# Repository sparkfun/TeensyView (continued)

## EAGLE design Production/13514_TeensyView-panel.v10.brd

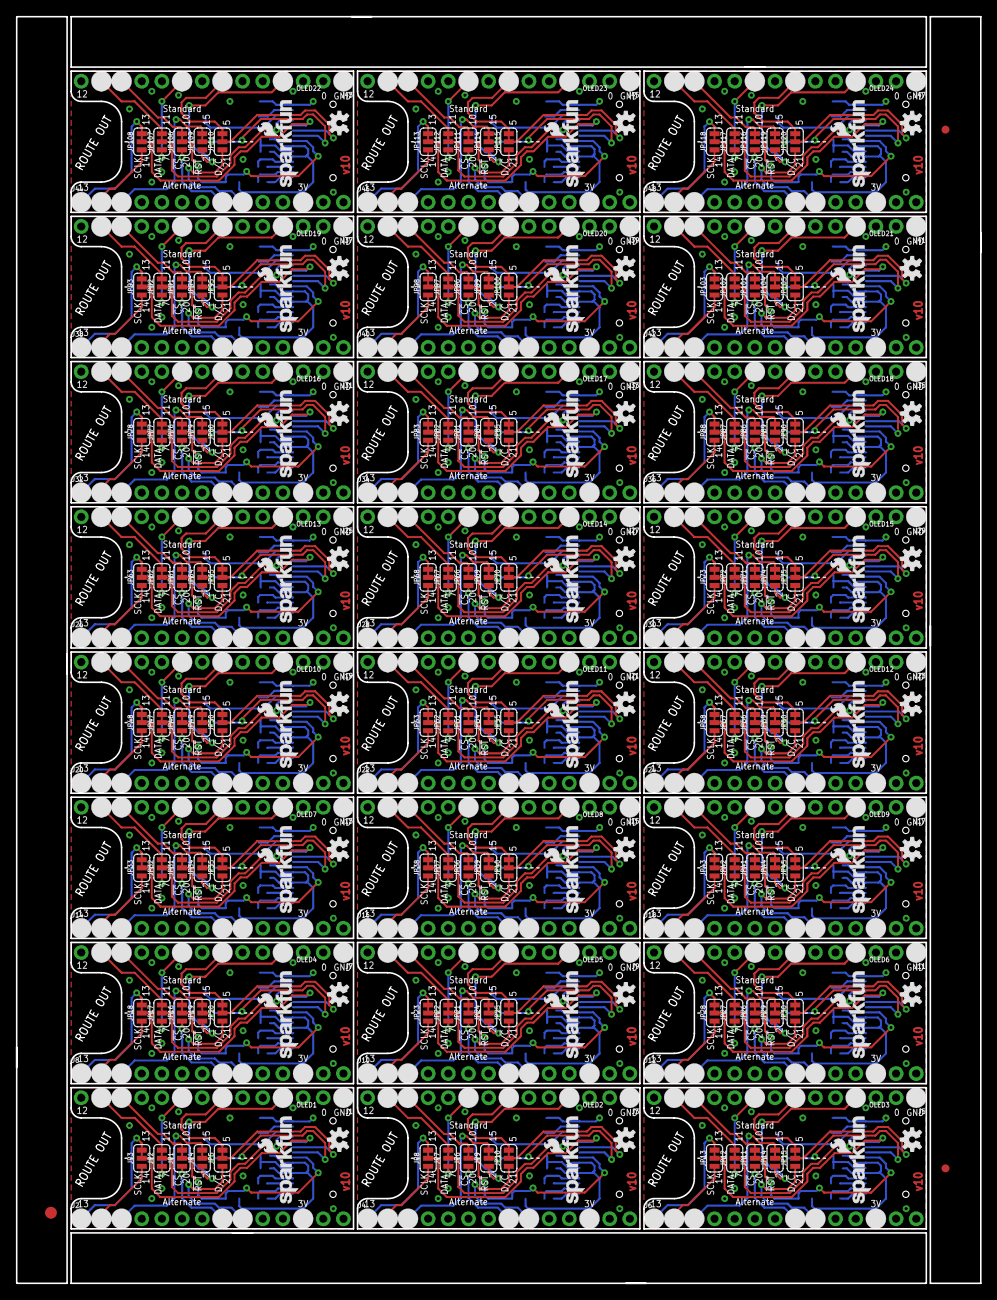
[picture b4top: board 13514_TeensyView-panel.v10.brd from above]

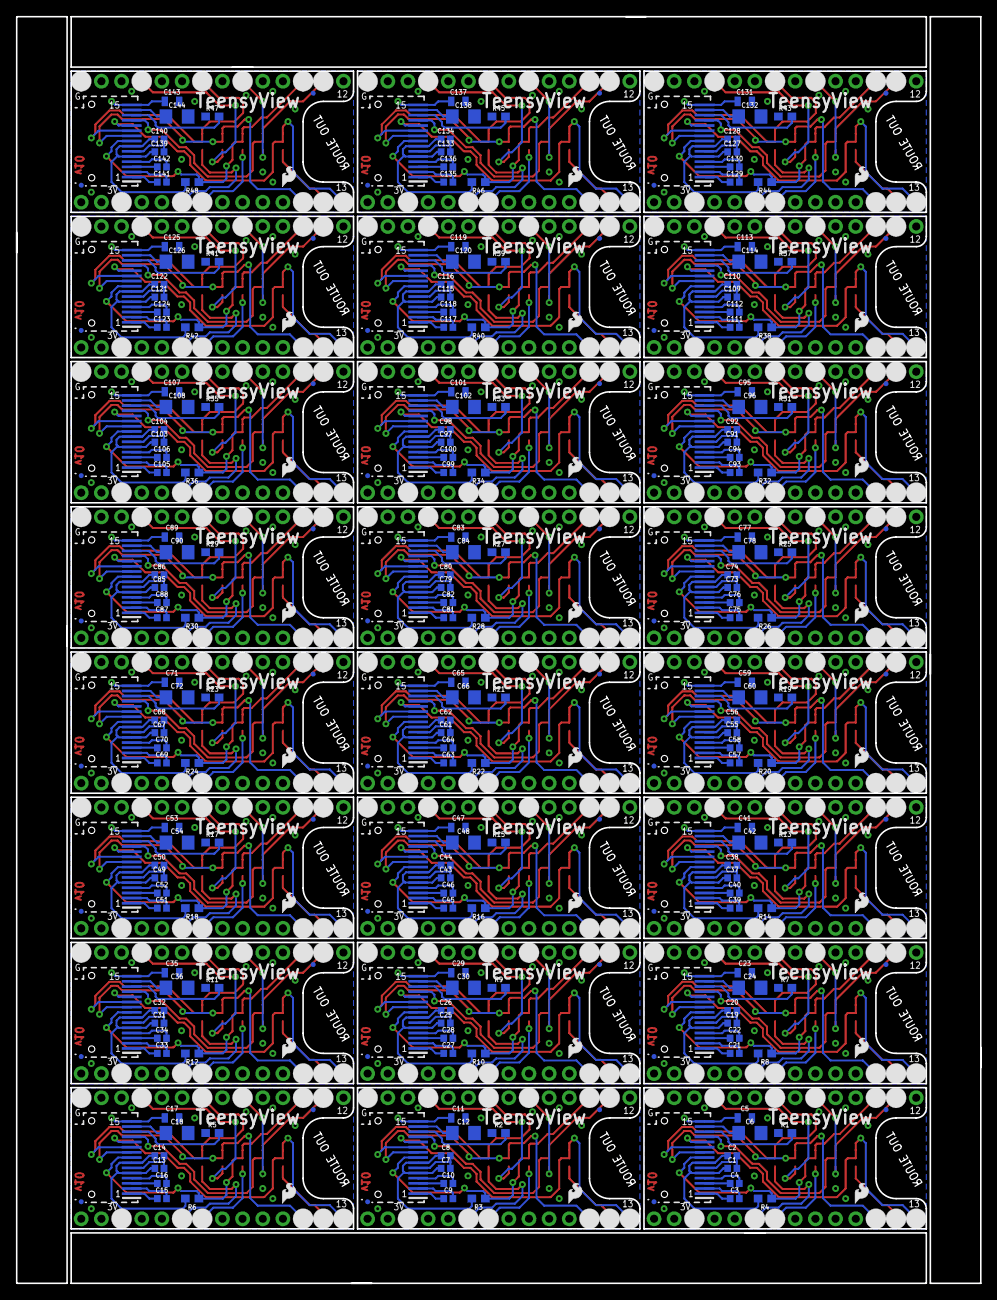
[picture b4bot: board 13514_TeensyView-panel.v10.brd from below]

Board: 2 copper layers, 121.4 x 159.5 mm, 531 parts (288 on the bottom side), 576 nets.

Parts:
C1, C2, C3, C4, C7, C8, C9, C10, C13, C14, C15, C16, C19, C20, C21, C22, C25, C26, C27, C28, C31, C32, C33, C34, C37, C38, C39, C40, C43, C44, C45, C46, C49, C50, C51, C52, C55, C56, C57, C58, C61, C62, C63, C64, C67, C68, C69, C70, C73, C74, C75, C76, C79, C80, C81, C82, C85, C86, C87, C88, C91, C92, C93, C94, C97, C98, C99, C100, C103, C104, C105, C106, C109, C110, C111, C112, C115, C116, C117, C118, C121, C122, C123, C124, C127, C128, C129, C130, C133, C134, C135, C136, C139, C140, C141, C142: 1.0uF; 0402
C5, C11, C17, C23, C29, C35, C41, C47, C53, C59, C65, C71, C77, C83, C89, C95, C101, C107, C113, C119, C125, C131, C137, C143: 2.2uF; 0805
C6, C12, C18, C24, C30, C36, C42, C48, C54, C60, C66, C72, C78, C84, C90, C96, C102, C108, C114, C120, C126, C132, C138, C144: 4.7uF; 1206
E$1: FIDUCIAL-1.5X3
E$7, E$8: FIDUCIAL-1X2
FD1, FD2, FD3, FD4, FD5, FD6, FD7, FD8, FD9, FD10, FD11, FD12, FD13, FD14, FD15, FD16, FD17, FD18, FD19, FD20, FD21, FD22, FD23, FD24, FD25, FD26, FD27, FD28, FD29, FD30, FD31, FD32, FD33, FD34, FD35, FD36, FD37, FD38, FD39, FD40, FD41, FD42, FD43, FD44, FD45, FD46, FD47, FD48: FIDUCIALUFIDUCIAL; FIDUCIAL-MICRO
J1, J2, J3, J4, J5, J6, J7, J8, J9, J10, J11, J12, J13, J14, J15, J16, J17, J18, J19, J20, J21, J22, J23, J24, J25, J26, J27, J28, J29, J30, J31, J32, J33, J34, J35, J36, J37, J38, J39, J40, J41, J42, J43, J44, J45, J46, J47, J48: DNP; 1X14_NO_SILK
JP1, JP2, JP3, JP4, JP5, JP6, JP7, JP8, JP9, JP10, JP11, JP12, JP13, JP14, JP15, JP16, JP17, JP18, JP19, JP20, JP21, JP22, JP23, JP24, JP25, JP26, JP27, JP28, JP29, JP30, JP31, JP32, JP33, JP34, JP35, JP36, JP37, JP38, JP39, JP40, JP41, JP42, JP43, JP44, JP45, JP46, JP47, JP48, JP49, JP50, JP51, JP52, JP53, JP54, JP55, JP56, JP57, JP58, JP59, JP60, JP61, JP62, JP63, JP64, JP65, JP66, JP67, JP68, JP69, JP70, JP71, JP72, JP73, JP74, JP75, JP76, JP77, JP78, JP79, JP80, JP81, JP82, JP83, JP84, JP85, JP86, JP87, JP88, JP89, JP90, JP91, JP92, JP93, JP94, JP95, JP96, JP97, JP98, JP99, JP100, JP101, JP102, JP103, JP104, JP105, JP106, JP107, JP108, JP109, JP110, JP111, JP112, JP113, JP114, JP115, JP116, JP117, JP118, JP119, JP120: JUMPER-SMT_3_1-NC_TRACE_SILK; SMT-JUMPER_3_1-NC_TRACE_SILK
LOGO1, LOGO4, LOGO7, LOGO10, LOGO13, LOGO16, LOGO19, LOGO22, LOGO25, LOGO28, LOGO31, LOGO34, LOGO37, LOGO40, LOGO43, LOGO46, LOGO49, LOGO52, LOGO55, LOGO58, LOGO61, LOGO64, LOGO67, LOGO70: SFE_LOGO_FLAME.1_INCH; SFE_LOGO_FLAME_.1
LOGO2, LOGO5, LOGO8, LOGO11, LOGO14, LOGO17, LOGO20, LOGO23, LOGO26, LOGO29, LOGO32, LOGO35, LOGO38, LOGO41, LOGO44, LOGO47, LOGO50, LOGO53, LOGO56, LOGO59, LOGO62, LOGO65, LOGO68, LOGO71: OSHW-LOGOS; OSHW-LOGO-S
LOGO3, LOGO6, LOGO9, LOGO12, LOGO15, LOGO18, LOGO21, LOGO24, LOGO27, LOGO30, LOGO33, LOGO36, LOGO39, LOGO42, LOGO45, LOGO48, LOGO51, LOGO54, LOGO57, LOGO60, LOGO63, LOGO66, LOGO69, LOGO72: SFE_LOGO_NAME_FLAME.1_INCH; SFE_LOGO_NAME_FLAME_.1
OLED1, OLED2, OLED3, OLED4, OLED5, OLED6, OLED7, OLED8, OLED9, OLED10, OLED11, OLED12, OLED13, OLED14, OLED15, OLED16, OLED17, OLED18, OLED19, OLED20, OLED21, OLED22, OLED23, OLED24: 32x128 OLED; OLED-UG-2832TSWGG01-REAR
R1, R2, R5, R7, R9, R11, R13, R15, R17, R19, R21, R23, R25, R27, R29, R31, R33, R35, R37, R39, R41, R43, R45, R47: 390k; 0603
R3, R4, R6, R8, R10, R12, R14, R16, R18, R20, R22, R24, R26, R28, R30, R32, R34, R36, R38, R40, R42, R44, R46, R48: 4.7k; 0603
TP1, TP2, TP3, TP4, TP5, TP6, TP7, TP8, TP9, TP10, TP11, TP12, TP13, TP14, TP15, TP16, TP17, TP18, TP19, TP20, TP21, TP22, TP23, TP24: TEST-POINTTP_15TH_THRU; TP_15TH

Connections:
!CS: JP1.2, OLED1.8, R4.1
!CS1: JP6.2, OLED2.8, R3.1
!CS2: JP11.2, OLED3.8, R6.1
!CS3: JP16.2, OLED4.8, R8.1
!CS4: JP21.2, OLED5.8, R10.1
!CS5: JP26.2, OLED6.8, R12.1
!CS6: JP31.2, OLED7.8, R14.1
!CS7: JP36.2, OLED8.8, R16.1
!CS8: JP41.2, OLED9.8, R18.1
!CS9: JP46.2, OLED10.8, R20.1
!CS10: JP51.2, OLED11.8, R22.1
!CS11: JP56.2, OLED12.8, R24.1
!CS12: JP61.2, OLED13.8, R26.1
!CS13: JP66.2, OLED14.8, R28.1
!CS14: JP71.2, OLED15.8, R30.1
!CS15: JP76.2, OLED16.8, R32.1
!CS16: JP81.2, OLED17.8, R34.1
!CS17: JP86.2, OLED18.8, R36.1
!CS18: JP91.2, OLED19.8, R38.1
!CS19: JP96.2, OLED20.8, R40.1
!CS20: JP101.2, OLED21.8, R42.1
!CS21: JP106.2, OLED22.8, R44.1
!CS22: JP111.2, OLED23.8, R46.1
!CS23: JP116.2, OLED24.8, R48.1
!RESET: JP4.2, OLED1.9
!RESET1: JP9.2, OLED2.9
!RESET2: JP14.2, OLED3.9
!RESET3: JP19.2, OLED4.9
!RESET4: JP24.2, OLED5.9
!RESET5: JP29.2, OLED6.9
!RESET6: JP34.2, OLED7.9
!RESET7: JP39.2, OLED8.9
!RESET8: JP44.2, OLED9.9
!RESET9: JP49.2, OLED10.9
!RESET10: JP54.2, OLED11.9
!RESET11: JP59.2, OLED12.9
!RESET12: JP64.2, OLED13.9
!RESET13: JP69.2, OLED14.9
!RESET14: JP74.2, OLED15.9
!RESET15: JP79.2, OLED16.9
!RESET16: JP84.2, OLED17.9
!RESET17: JP89.2, OLED18.9
!RESET18: JP94.2, OLED19.9
!RESET19: JP99.2, OLED20.9
!RESET20: JP104.2, OLED21.9
!RESET21: JP109.2, OLED22.9
!RESET22: JP114.2, OLED23.9
!RESET23: JP119.2, OLED24.9
D/!C: JP5.2, OLED1.10
D/!C1: JP10.2, OLED2.10
D/!C2: JP15.2, OLED3.10
D/!C3: JP20.2, OLED4.10
D/!C4: JP25.2, OLED5.10
D/!C5: JP30.2, OLED6.10
D/!C6: JP35.2, OLED7.10
D/!C7: JP40.2, OLED8.10
D/!C8: JP45.2, OLED9.10
D/!C9: JP50.2, OLED10.10
D/!C10: JP55.2, OLED11.10
D/!C11: JP60.2, OLED12.10
D/!C12: JP65.2, OLED13.10
D/!C13: JP70.2, OLED14.10
D/!C14: JP75.2, OLED15.10
D/!C15: JP80.2, OLED16.10
D/!C16: JP85.2, OLED17.10
D/!C17: JP90.2, OLED18.10
D/!C18: JP95.2, OLED19.10
D/!C19: JP100.2, OLED20.10
D/!C20: JP105.2, OLED21.10
D/!C21: JP110.2, OLED22.10
D/!C22: JP115.2, OLED23.10
D/!C23: JP120.2, OLED24.10
GND: C1.2, C2.2, C5.2, C6.2, J1.1, OLED1.6, R1.1
GND1: C7.2, C8.2, C11.2, C12.2, J3.1, OLED2.6, R2.1
GND2: C13.2, C14.2, C17.2, C18.2, J5.1, OLED3.6, R5.1
GND3: C19.2, C20.2, C23.2, C24.2, J7.1, OLED4.6, R7.1
GND4: C25.2, C26.2, C29.2, C30.2, J9.1, OLED5.6, R9.1
GND5: C31.2, C32.2, C35.2, C36.2, J11.1, OLED6.6, R11.1
GND6: C37.2, C38.2, C41.2, C42.2, J13.1, OLED7.6, R13.1
GND7: C43.2, C44.2, C47.2, C48.2, J15.1, OLED8.6, R15.1
GND8: C49.2, C50.2, C53.2, C54.2, J17.1, OLED9.6, R17.1
GND9: C55.2, C56.2, C59.2, C60.2, J19.1, OLED10.6, R19.1
GND10: C61.2, C62.2, C65.2, C66.2, J21.1, OLED11.6, R21.1
GND11: C67.2, C68.2, C71.2, C72.2, J23.1, OLED12.6, R23.1
GND12: C73.2, C74.2, C77.2, C78.2, J25.1, OLED13.6, R25.1
GND13: C79.2, C80.2, C83.2, C84.2, J27.1, OLED14.6, R27.1
GND14: C85.2, C86.2, C89.2, C90.2, J29.1, OLED15.6, R29.1
GND15: C91.2, C92.2, C95.2, C96.2, J31.1, OLED16.6, R31.1
GND16: C97.2, C98.2, C101.2, C102.2, J33.1, OLED17.6, R33.1
GND17: C103.2, C104.2, C107.2, C108.2, J35.1, OLED18.6, R35.1
GND18: C109.2, C110.2, C113.2, C114.2, J37.1, OLED19.6, R37.1
GND19: C115.2, C116.2, C119.2, C120.2, J39.1, OLED20.6, R39.1
GND20: C121.2, C122.2, C125.2, C126.2, J41.1, OLED21.6, R41.1
GND21: C127.2, C128.2, C131.2, C132.2, J43.1, OLED22.6, R43.1
GND22: C133.2, C134.2, C137.2, C138.2, J45.1, OLED23.6, R45.1
GND23: C139.2, C140.2, C143.2, C144.2, J47.1, OLED24.6, R47.1
unnamed: J1.12, JP1.3
unnamed: J2.8, JP1.1
unnamed: C4.2, OLED1.4
unnamed: C4.1, OLED1.3
unnamed: C3.2, OLED1.2
unnamed: C3.1, OLED1.1
unnamed: OLED1.13, R1.2
unnamed: C6.1, OLED1.14
unnamed: C5.1, OLED1.15, TP1.P$1
unnamed: J2.1, JP3.3
unnamed: J2.2, JP3.1
unnamed: J1.13, JP2.3
unnamed: J1.9, JP2.1
unnamed: J2.3, JP4.3
unnamed: J1.4, JP4.1
unnamed: J1.7, JP5.3
unnamed: J2.9, JP5.1
unnamed: C10.2, OLED2.4
unnamed: C10.1, OLED2.3
unnamed: C9.2, OLED2.2
unnamed: C9.1, OLED2.1
unnamed: OLED2.13, R2.2
unnamed: C12.1, OLED2.14
unnamed: C11.1, OLED2.15, TP2.P$1
unnamed: J3.12, JP6.3
unnamed: J4.2, JP8.1
unnamed: J4.1, JP8.3
unnamed: J3.13, JP7.3
unnamed: J3.9, JP7.1
unnamed: J4.8, JP6.1
unnamed: J4.3, JP9.3
unnamed: J3.4, JP9.1
unnamed: J3.7, JP10.3
unnamed: J4.9, JP10.1
unnamed: C16.2, OLED3.4
unnamed: C16.1, OLED3.3
unnamed: C15.2, OLED3.2
unnamed: C15.1, OLED3.1
unnamed: OLED3.13, R5.2
unnamed: C18.1, OLED3.14
unnamed: C17.1, OLED3.15, TP3.P$1
unnamed: J5.12, JP11.3
unnamed: J6.2, JP13.1
unnamed: J6.1, JP13.3
unnamed: J5.13, JP12.3
unnamed: J5.9, JP12.1
unnamed: J6.8, JP11.1
unnamed: J6.3, JP14.3
unnamed: J5.4, JP14.1
unnamed: J5.7, JP15.3
unnamed: J6.9, JP15.1
unnamed: C22.2, OLED4.4
unnamed: C22.1, OLED4.3
unnamed: C21.2, OLED4.2
unnamed: C21.1, OLED4.1
unnamed: OLED4.13, R7.2
unnamed: C24.1, OLED4.14
unnamed: C23.1, OLED4.15, TP4.P$1
unnamed: J7.12, JP16.3
unnamed: J8.2, JP18.1
unnamed: J8.1, JP18.3
unnamed: J7.13, JP17.3
unnamed: J7.9, JP17.1
unnamed: J8.8, JP16.1
unnamed: J8.3, JP19.3
unnamed: J7.4, JP19.1
unnamed: J7.7, JP20.3
unnamed: J8.9, JP20.1
unnamed: C28.2, OLED5.4
unnamed: C28.1, OLED5.3
unnamed: C27.2, OLED5.2
unnamed: C27.1, OLED5.1
unnamed: OLED5.13, R9.2
unnamed: C30.1, OLED5.14
unnamed: C29.1, OLED5.15, TP5.P$1
unnamed: J9.12, JP21.3
unnamed: J10.2, JP23.1
unnamed: J10.1, JP23.3
unnamed: J9.13, JP22.3
unnamed: J9.9, JP22.1
unnamed: J10.8, JP21.1
unnamed: J10.3, JP24.3
unnamed: J9.4, JP24.1
unnamed: J9.7, JP25.3
unnamed: J10.9, JP25.1
unnamed: C34.2, OLED6.4
unnamed: C34.1, OLED6.3
unnamed: C33.2, OLED6.2
unnamed: C33.1, OLED6.1
unnamed: OLED6.13, R11.2
unnamed: C36.1, OLED6.14
unnamed: C35.1, OLED6.15, TP6.P$1
unnamed: J11.12, JP26.3
unnamed: J12.2, JP28.1
unnamed: J12.1, JP28.3
unnamed: J11.13, JP27.3
unnamed: J11.9, JP27.1
unnamed: J12.8, JP26.1
unnamed: J12.3, JP29.3
unnamed: J11.4, JP29.1
unnamed: J11.7, JP30.3
unnamed: J12.9, JP30.1
unnamed: C40.2, OLED7.4
unnamed: C40.1, OLED7.3
unnamed: C39.2, OLED7.2
unnamed: C39.1, OLED7.1
unnamed: OLED7.13, R13.2
unnamed: C42.1, OLED7.14
unnamed: C41.1, OLED7.15, TP7.P$1
unnamed: J13.12, JP31.3
unnamed: J14.2, JP33.1
unnamed: J14.1, JP33.3
unnamed: J13.13, JP32.3
unnamed: J13.9, JP32.1
unnamed: J14.8, JP31.1
unnamed: J14.3, JP34.3
unnamed: J13.4, JP34.1
unnamed: J13.7, JP35.3
unnamed: J14.9, JP35.1
unnamed: C46.2, OLED8.4
unnamed: C46.1, OLED8.3
unnamed: C45.2, OLED8.2
unnamed: C45.1, OLED8.1
unnamed: OLED8.13, R15.2
unnamed: C48.1, OLED8.14
unnamed: C47.1, OLED8.15, TP8.P$1
unnamed: J15.12, JP36.3
unnamed: J16.2, JP38.1
unnamed: J16.1, JP38.3
unnamed: J15.13, JP37.3
unnamed: J15.9, JP37.1
unnamed: J16.8, JP36.1
unnamed: J16.3, JP39.3
unnamed: J15.4, JP39.1
unnamed: J15.7, JP40.3
unnamed: J16.9, JP40.1
unnamed: C52.2, OLED9.4
unnamed: C52.1, OLED9.3
unnamed: C51.2, OLED9.2
unnamed: C51.1, OLED9.1
unnamed: OLED9.13, R17.2
unnamed: C54.1, OLED9.14
unnamed: C53.1, OLED9.15, TP9.P$1
unnamed: J17.12, JP41.3
unnamed: J18.2, JP43.1
unnamed: J18.1, JP43.3
unnamed: J17.13, JP42.3
unnamed: J17.9, JP42.1
unnamed: J18.8, JP41.1
unnamed: J18.3, JP44.3
unnamed: J17.4, JP44.1
unnamed: J17.7, JP45.3
unnamed: J18.9, JP45.1
unnamed: C58.2, OLED10.4
unnamed: C58.1, OLED10.3
unnamed: C57.2, OLED10.2
unnamed: C57.1, OLED10.1
unnamed: OLED10.13, R19.2
unnamed: C60.1, OLED10.14
unnamed: C59.1, OLED10.15, TP10.P$1
unnamed: J19.12, JP46.3
unnamed: J20.2, JP48.1
unnamed: J20.1, JP48.3
unnamed: J19.13, JP47.3
unnamed: J19.9, JP47.1
unnamed: J20.8, JP46.1
unnamed: J20.3, JP49.3
unnamed: J19.4, JP49.1
unnamed: J19.7, JP50.3
unnamed: J20.9, JP50.1
unnamed: C64.2, OLED11.4
unnamed: C64.1, OLED11.3
unnamed: C63.2, OLED11.2
unnamed: C63.1, OLED11.1
unnamed: OLED11.13, R21.2
unnamed: C66.1, OLED11.14
unnamed: C65.1, OLED11.15, TP11.P$1
unnamed: J21.12, JP51.3
unnamed: J22.2, JP53.1
unnamed: J22.1, JP53.3
unnamed: J21.13, JP52.3
unnamed: J21.9, JP52.1
unnamed: J22.8, JP51.1
unnamed: J22.3, JP54.3
unnamed: J21.4, JP54.1
unnamed: J21.7, JP55.3
unnamed: J22.9, JP55.1
unnamed: C70.2, OLED12.4
unnamed: C70.1, OLED12.3
unnamed: C69.2, OLED12.2
unnamed: C69.1, OLED12.1
unnamed: OLED12.13, R23.2
unnamed: C72.1, OLED12.14
unnamed: C71.1, OLED12.15, TP12.P$1
unnamed: J23.12, JP56.3
unnamed: J24.2, JP58.1
unnamed: J24.1, JP58.3
unnamed: J23.13, JP57.3
unnamed: J23.9, JP57.1
unnamed: J24.8, JP56.1
unnamed: J24.3, JP59.3
unnamed: J23.4, JP59.1
unnamed: J23.7, JP60.3
unnamed: J24.9, JP60.1
unnamed: C76.2, OLED13.4
unnamed: C76.1, OLED13.3
unnamed: C75.2, OLED13.2
unnamed: C75.1, OLED13.1
unnamed: OLED13.13, R25.2
unnamed: C78.1, OLED13.14
unnamed: C77.1, OLED13.15, TP13.P$1
unnamed: J25.12, JP61.3
unnamed: J26.2, JP63.1
unnamed: J26.1, JP63.3
unnamed: J25.13, JP62.3
unnamed: J25.9, JP62.1
unnamed: J26.8, JP61.1
unnamed: J26.3, JP64.3
unnamed: J25.4, JP64.1
unnamed: J25.7, JP65.3
unnamed: J26.9, JP65.1
unnamed: C82.2, OLED14.4
unnamed: C82.1, OLED14.3
unnamed: C81.2, OLED14.2
unnamed: C81.1, OLED14.1
unnamed: OLED14.13, R27.2
unnamed: C84.1, OLED14.14
unnamed: C83.1, OLED14.15, TP14.P$1
unnamed: J27.12, JP66.3
unnamed: J28.2, JP68.1
unnamed: J28.1, JP68.3
unnamed: J27.13, JP67.3
unnamed: J27.9, JP67.1
unnamed: J28.8, JP66.1
unnamed: J28.3, JP69.3
unnamed: J27.4, JP69.1
unnamed: J27.7, JP70.3
unnamed: J28.9, JP70.1
unnamed: C88.2, OLED15.4
unnamed: C88.1, OLED15.3
unnamed: C87.2, OLED15.2
unnamed: C87.1, OLED15.1
unnamed: OLED15.13, R29.2
unnamed: C90.1, OLED15.14
unnamed: C89.1, OLED15.15, TP15.P$1
unnamed: J29.12, JP71.3
unnamed: J30.2, JP73.1
unnamed: J30.1, JP73.3
unnamed: J29.13, JP72.3
unnamed: J29.9, JP72.1
unnamed: J30.8, JP71.1
unnamed: J30.3, JP74.3
unnamed: J29.4, JP74.1
unnamed: J29.7, JP75.3
unnamed: J30.9, JP75.1
unnamed: C94.2, OLED16.4
unnamed: C94.1, OLED16.3
unnamed: C93.2, OLED16.2
unnamed: C93.1, OLED16.1
unnamed: OLED16.13, R31.2
unnamed: C96.1, OLED16.14
unnamed: C95.1, OLED16.15, TP16.P$1
unnamed: J31.12, JP76.3
unnamed: J32.2, JP78.1
unnamed: J32.1, JP78.3
unnamed: J31.13, JP77.3
unnamed: J31.9, JP77.1
unnamed: J32.8, JP76.1
unnamed: J32.3, JP79.3
unnamed: J31.4, JP79.1
unnamed: J31.7, JP80.3
unnamed: J32.9, JP80.1
unnamed: C100.2, OLED17.4
unnamed: C100.1, OLED17.3
unnamed: C99.2, OLED17.2
unnamed: C99.1, OLED17.1
unnamed: OLED17.13, R33.2
unnamed: C102.1, OLED17.14
unnamed: C101.1, OLED17.15, TP17.P$1
unnamed: J33.12, JP81.3
unnamed: J34.2, JP83.1
unnamed: J34.1, JP83.3
unnamed: J33.13, JP82.3
unnamed: J33.9, JP82.1
unnamed: J34.8, JP81.1
unnamed: J34.3, JP84.3
unnamed: J33.4, JP84.1
unnamed: J33.7, JP85.3
unnamed: J34.9, JP85.1
unnamed: C106.2, OLED18.4
unnamed: C106.1, OLED18.3
unnamed: C105.2, OLED18.2
unnamed: C105.1, OLED18.1
unnamed: OLED18.13, R35.2
unnamed: C108.1, OLED18.14
unnamed: C107.1, OLED18.15, TP18.P$1
unnamed: J35.12, JP86.3
unnamed: J36.2, JP88.1
unnamed: J36.1, JP88.3
unnamed: J35.13, JP87.3
unnamed: J35.9, JP87.1
unnamed: J36.8, JP86.1
unnamed: J36.3, JP89.3
unnamed: J35.4, JP89.1
unnamed: J35.7, JP90.3
unnamed: J36.9, JP90.1
unnamed: C112.2, OLED19.4
unnamed: C112.1, OLED19.3
unnamed: C111.2, OLED19.2
unnamed: C111.1, OLED19.1
unnamed: OLED19.13, R37.2
unnamed: C114.1, OLED19.14
unnamed: C113.1, OLED19.15, TP19.P$1
unnamed: J37.12, JP91.3
unnamed: J38.2, JP93.1
unnamed: J38.1, JP93.3
unnamed: J37.13, JP92.3
unnamed: J37.9, JP92.1
unnamed: J38.8, JP91.1
unnamed: J38.3, JP94.3
unnamed: J37.4, JP94.1
unnamed: J37.7, JP95.3
unnamed: J38.9, JP95.1
unnamed: C118.2, OLED20.4
unnamed: C118.1, OLED20.3
unnamed: C117.2, OLED20.2
unnamed: C117.1, OLED20.1
unnamed: OLED20.13, R39.2
unnamed: C120.1, OLED20.14
unnamed: C119.1, OLED20.15, TP20.P$1
unnamed: J39.12, JP96.3
unnamed: J40.2, JP98.1
unnamed: J40.1, JP98.3
unnamed: J39.13, JP97.3
unnamed: J39.9, JP97.1
unnamed: J40.8, JP96.1
unnamed: J40.3, JP99.3
unnamed: J39.4, JP99.1
unnamed: J39.7, JP100.3
unnamed: J40.9, JP100.1
unnamed: C124.2, OLED21.4
unnamed: C124.1, OLED21.3
unnamed: C123.2, OLED21.2
unnamed: C123.1, OLED21.1
unnamed: OLED21.13, R41.2
unnamed: C126.1, OLED21.14
unnamed: C125.1, OLED21.15, TP21.P$1
unnamed: J41.12, JP101.3
unnamed: J42.2, JP103.1
unnamed: J42.1, JP103.3
unnamed: J41.13, JP102.3
unnamed: J41.9, JP102.1
unnamed: J42.8, JP101.1
unnamed: J42.3, JP104.3
unnamed: J41.4, JP104.1
unnamed: J41.7, JP105.3
unnamed: J42.9, JP105.1
unnamed: C130.2, OLED22.4
unnamed: C130.1, OLED22.3
unnamed: C129.2, OLED22.2
unnamed: C129.1, OLED22.1
unnamed: OLED22.13, R43.2
unnamed: C132.1, OLED22.14
unnamed: C131.1, OLED22.15, TP22.P$1
unnamed: J43.12, JP106.3
unnamed: J44.2, JP108.1
unnamed: J44.1, JP108.3
unnamed: J43.13, JP107.3
unnamed: J43.9, JP107.1
unnamed: J44.8, JP106.1
unnamed: J44.3, JP109.3
unnamed: J43.4, JP109.1
unnamed: J43.7, JP110.3
unnamed: J44.9, JP110.1
unnamed: C136.2, OLED23.4
unnamed: C136.1, OLED23.3
unnamed: C135.2, OLED23.2
unnamed: C135.1, OLED23.1
unnamed: OLED23.13, R45.2
unnamed: C138.1, OLED23.14
unnamed: C137.1, OLED23.15, TP23.P$1
unnamed: J45.12, JP111.3
unnamed: J46.2, JP113.1
unnamed: J46.1, JP113.3
unnamed: J45.13, JP112.3
unnamed: J45.9, JP112.1
unnamed: J46.8, JP111.1
unnamed: J46.3, JP114.3
unnamed: J45.4, JP114.1
unnamed: J45.7, JP115.3
unnamed: J46.9, JP115.1
unnamed: C142.2, OLED24.4
unnamed: C142.1, OLED24.3
unnamed: C141.2, OLED24.2
unnamed: C141.1, OLED24.1
unnamed: OLED24.13, R47.2
unnamed: C144.1, OLED24.14
unnamed: C143.1, OLED24.15, TP24.P$1
unnamed: J47.12, JP116.3
unnamed: J48.2, JP118.1
unnamed: J48.1, JP118.3
unnamed: J47.13, JP117.3
unnamed: J47.9, JP117.1
unnamed: J48.8, JP116.1
unnamed: J48.3, JP119.3
unnamed: J47.4, JP119.1
unnamed: J47.7, JP120.3
unnamed: J48.9, JP120.1
SCLK: JP3.2, OLED1.11
SCLK1: JP8.2, OLED2.11
SCLK2: JP13.2, OLED3.11
SCLK3: JP18.2, OLED4.11
SCLK4: JP23.2, OLED5.11
SCLK5: JP28.2, OLED6.11
SCLK6: JP33.2, OLED7.11
SCLK7: JP38.2, OLED8.11
SCLK8: JP43.2, OLED9.11
SCLK9: JP48.2, OLED10.11
SCLK10: JP53.2, OLED11.11
SCLK11: JP58.2, OLED12.11
SCLK12: JP63.2, OLED13.11
SCLK13: JP68.2, OLED14.11
SCLK14: JP73.2, OLED15.11
SCLK15: JP78.2, OLED16.11
SCLK16: JP83.2, OLED17.11
SCLK17: JP88.2, OLED18.11
SCLK18: JP93.2, OLED19.11
SCLK19: JP98.2, OLED20.11
SCLK20: JP103.2, OLED21.11
SCLK21: JP108.2, OLED22.11
SCLK22: JP113.2, OLED23.11
SCLK23: JP118.2, OLED24.11
SDIN: JP2.2, OLED1.12
SDIN1: JP7.2, OLED2.12
SDIN2: JP12.2, OLED3.12
SDIN3: JP17.2, OLED4.12
SDIN4: JP22.2, OLED5.12
SDIN5: JP27.2, OLED6.12
SDIN6: JP32.2, OLED7.12
SDIN7: JP37.2, OLED8.12
SDIN8: JP42.2, OLED9.12
SDIN9: JP47.2, OLED10.12
SDIN10: JP52.2, OLED11.12
SDIN11: JP57.2, OLED12.12
SDIN12: JP62.2, OLED13.12
SDIN13: JP67.2, OLED14.12
SDIN14: JP72.2, OLED15.12
SDIN15: JP77.2, OLED16.12
SDIN16: JP82.2, OLED17.12
SDIN17: JP87.2, OLED18.12
SDIN18: JP92.2, OLED19.12
SDIN19: JP97.2, OLED20.12
SDIN20: JP102.2, OLED21.12
SDIN21: JP107.2, OLED22.12
SDIN22: JP112.2, OLED23.12
SDIN23: JP117.2, OLED24.12
VCC: C1.1, C2.1, J2.12, OLED1.5, OLED1.7, R4.2
VCC1: C7.1, C8.1, J4.12, OLED2.5, OLED2.7, R3.2
VCC2: C13.1, C14.1, J6.12, OLED3.5, OLED3.7, R6.2
VCC3: C19.1, C20.1, J8.12, OLED4.5, OLED4.7, R8.2
VCC4: C25.1, C26.1, J10.12, OLED5.5, OLED5.7, R10.2
VCC5: C31.1, C32.1, J12.12, OLED6.5, OLED6.7, R12.2
VCC6: C37.1, C38.1, J14.12, OLED7.5, OLED7.7, R14.2
VCC7: C43.1, C44.1, J16.12, OLED8.5, OLED8.7, R16.2
VCC8: C49.1, C50.1, J18.12, OLED9.5, OLED9.7, R18.2
VCC9: C55.1, C56.1, J20.12, OLED10.5, OLED10.7, R20.2
VCC10: C61.1, C62.1, J22.12, OLED11.5, OLED11.7, R22.2
VCC11: C67.1, C68.1, J24.12, OLED12.5, OLED12.7, R24.2
VCC12: C73.1, C74.1, J26.12, OLED13.5, OLED13.7, R26.2
VCC13: C79.1, C80.1, J28.12, OLED14.5, OLED14.7, R28.2
VCC14: C85.1, C86.1, J30.12, OLED15.5, OLED15.7, R30.2
VCC15: C91.1, C92.1, J32.12, OLED16.5, OLED16.7, R32.2
VCC16: C97.1, C98.1, J34.12, OLED17.5, OLED17.7, R34.2
VCC17: C103.1, C104.1, J36.12, OLED18.5, OLED18.7, R36.2
VCC18: C109.1, C110.1, J38.12, OLED19.5, OLED19.7, R38.2
VCC19: C115.1, C116.1, J40.12, OLED20.5, OLED20.7, R40.2
VCC20: C121.1, C122.1, J42.12, OLED21.5, OLED21.7, R42.2
VCC21: C127.1, C128.1, J44.12, OLED22.5, OLED22.7, R44.2
VCC22: C133.1, C134.1, J46.12, OLED23.5, OLED23.7, R46.2
VCC23: C139.1, C140.1, J48.12, OLED24.5, OLED24.7, R48.2

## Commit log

2016-08-25 Created basic PCB
2016-08-25 Added test boards to design
2016-09-12 Proto 1 design complete
2016-09-14 Post review fixes
2016-09-15 Resized dimension, moved 1 via and added a couple more
2016-12-05 Going for proto 2
2016-12-06 Moved silk.
2016-12-06 Applied Proto 2 review action items
2016-12-06 Added TP to OLED's VCC
2016-12-08 worked through checklist and updated some parts, moved TP
2017-01-06 Adjusted proto 2 in prep for reds review
2017-01-09 Made silk and version number changes for reds
2017-01-18 panel
2017-02-23 put links into readme
2017-03-15 Squashed 'Libraries/Arduino/' content from commit 0b28e56
    git-subtree-dir: Libraries/Arduino
    git-subtree-split: 0b28e5669c08754daa54997ed27a598d5a9bf809
2017-03-15 Updated Library root readme
2017-03-15 Fixed readme link
2017-04-19 FONTPITCH TeensyView Arduino Library
    Fixed character spacing issue. The spacing between characters using font5x7 (which is really 5x8) needs to be different than the spacing between characters using font8x16 because font8x16 already has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
2017-04-19 FONTPITCH TeensyView Arduino Library Update
    Added FONTPITCH to font5x7 (which is really 5x8).
2017-04-19 FONTPITCH TeensyView Arduino Library Update
    Added FONTPITCH to font8x16.
2017-04-19 FONTPITCH TeensyView Arduino Library Update
2019-02-25 added minus sign character.
    reformatted the array to facilitate editing.
2019-03-08 Add multiple spi support
2019-03-08 unify tab style to tab instead of spaces
2019-03-08 Create a demo for custom SPI port usage
    Currently not supporting alternate pin assignment on the SPI ports, but it should be fairly easy to use.
    Also not tested, but it compiles.
